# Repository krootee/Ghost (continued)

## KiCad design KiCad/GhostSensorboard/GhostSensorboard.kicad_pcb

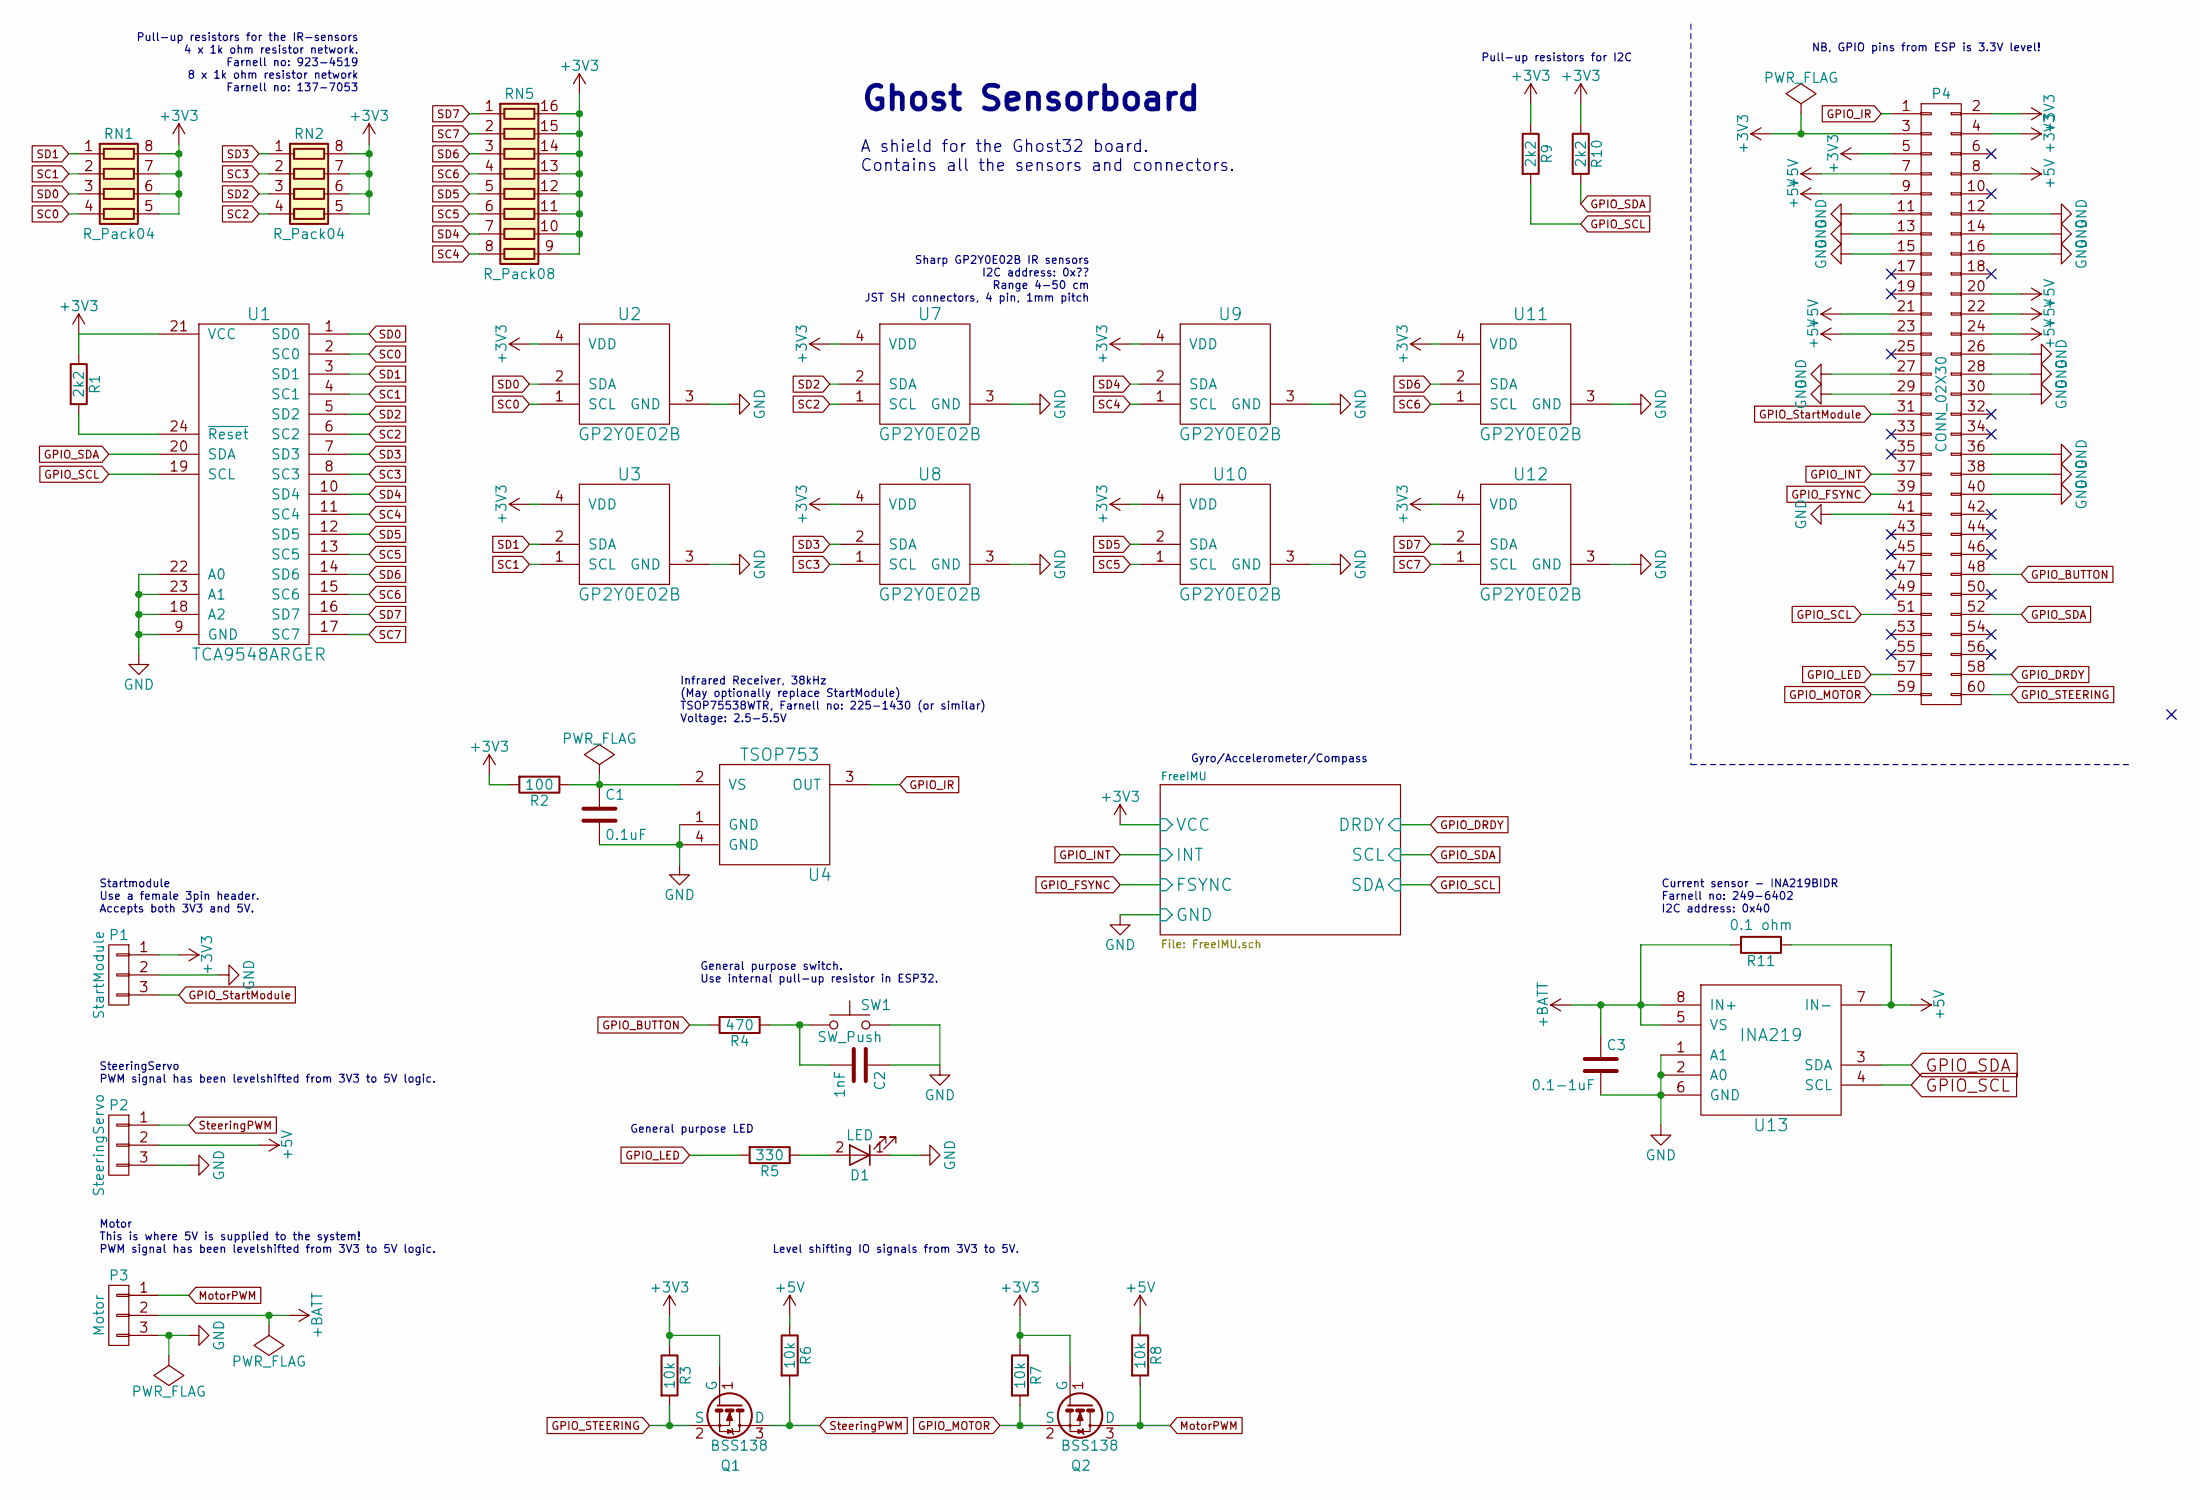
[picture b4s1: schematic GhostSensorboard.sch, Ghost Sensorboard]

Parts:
C1: 0.1uF; C_0603
C2: 1nF; C_0603
C3: 0.1-1uF; C_0603
D1: LED; LED_0805
P1: StartModule; Pin_Header_Straight_1x03_Pitch2.54mm
P2: SteeringServo; Pin_Header_Straight_1x03_Pitch2.54mm
P3: Motor; Pin_Header_Straight_1x03_Pitch2.54mm
P4: CONN_02X30; hrs-fx8c-60s-sv
Q1, Q2: BSS138; SOT-23
R1, R9, R10: 2k2; R_0603_HandSoldering
R2: 100; R_0603_HandSoldering
R3, R6, R7, R8: 10k; R_0603_HandSoldering
R4: 470; R_0603_HandSoldering
R5: 330; R_0603_HandSoldering
R11: 0.1 ohm; R_0603_HandSoldering
RN1, RN2: R_Pack04; R_Array_Convex_4x0603
RN5: R_Pack08; R_Array_Convex_8x0602
SW1: SW_Push; SW_SPST_EVQP2
U1: TCA9548ARGER; QFN-24_4x4mm_Pitch0.5mm
U2, U3, U7, U8, U9, U10, U11, U12: GP2Y0E02B; JST_SH_BM04B-SRSS-TB_04x1.00mm_Straight
U4: TSOP753; TSOP75x
U13: INA219; SOIC-8-N

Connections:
+3V3: P1.1, P4.2, P4.3, P4.4, P4.5, Q1.1 (G), Q2.1 (G), R1.1, R2.2, R3.1, R7.1, R9.1, R10.1, RN1.5 (R4.2), RN1.6 (R3.2), RN1.7 (R2.2), RN1.8 (R1.2), RN2.5 (R4.2), RN2.6 (R3.2), RN2.7 (R2.2), RN2.8 (R1.2), RN5.9 (R8.2), RN5.10 (R7.2), RN5.11 (R6.2), RN5.12 (R5.2), RN5.13 (R4.2), RN5.14 (R3.2), RN5.15 (R2.2), RN5.16 (R1.2), U1.21 (VCC), U2.4 (VDD), U3.4 (VDD), U7.4 (VDD), U8.4 (VDD), U9.4 (VDD), U10.4 (VDD), U11.4 (VDD), U12.4 (VDD); also elsewhere on the board
+5V: P2.2, P4.7, P4.8, P4.9, P4.20, P4.21, P4.22, P4.23, P4.24, R6.1, R8.1, R11.1, U13.7 (IN-)
+BATT: C3.1, P3.2, R11.2, U13.5 (VS), U13.8 (IN+)
GPIO_BUTTON: P4.48, R4.2
GPIO_DRDY: P4.58; also elsewhere on the board
GPIO_FSYNC: P4.39; also elsewhere on the board
GPIO_INT: P4.37; also elsewhere on the board
GPIO_IR: P4.1, U4.3 (OUT)
GPIO_LED: P4.57, R5.2
GPIO_MOTOR: P4.59, Q2.2 (S), R7.2
GPIO_SCL: P4.51, R9.2, U1.19 (SCL), U13.4 (SCL); also elsewhere on the board
GPIO_SDA: P4.52, R10.2, U1.20 (SDA), U13.3 (SDA); also elsewhere on the board
GPIO_STEERING: P4.60, Q1.2 (S), R3.2
GPIO_StartModule: P1.3, P4.31
MotorPWM: P3.1, Q2.3 (D), R8.2
unnamed: C1.1, R2.1, U4.2 (VS)
unnamed: C2.2, R4.1, SW1.1
unnamed: D1.2 (A), R5.1
unnamed: R1.2, U1.24 (~Reset)
SC0: RN1.4 (R4.1), U1.2 (SC0), U2.1 (SCL)
SC1: RN1.2 (R2.1), U1.4 (SC1), U3.1 (SCL)
SC2: RN2.4 (R4.1), U1.6 (SC2), U7.1 (SCL)
SC3: RN2.2 (R2.1), U1.8 (SC3), U8.1 (SCL)
SC4: RN5.8 (R8.1), U1.11 (SC4), U9.1 (SCL)
SC5: RN5.6 (R6.1), U1.13 (SC5), U10.1 (SCL)
SC6: RN5.4 (R4.1), U1.15 (SC6), U11.1 (SCL)
SC7: RN5.2 (R2.1), U1.17 (SC7), U12.1 (SCL)
SD0: RN1.3 (R3.1), U1.1 (SD0), U2.2 (SDA)
SD1: RN1.1 (R1.1), U1.3 (SD1), U3.2 (SDA)
SD2: RN2.3 (R3.1), U1.5 (SD2), U7.2 (SDA)
SD3: RN2.1 (R1.1), U1.7 (SD3), U8.2 (SDA)
SD4: RN5.7 (R7.1), U1.10 (SD4), U9.2 (SDA)
SD5: RN5.5 (R5.1), U1.12 (SD5), U10.2 (SDA)
SD6: RN5.3 (R3.1), U1.14 (SD6), U11.2 (SDA)
SD7: RN5.1 (R1.1), U1.16 (SD7), U12.2 (SDA)
SteeringPWM: P2.1, Q1.3 (D), R6.2

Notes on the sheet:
Ghost Sensorboard
A shield for the Ghost32 board. Contains all the sensors and connectors.
NB, GPIO pins from ESP is 3.3V level!
Startmodule Use a female 3pin header. Accepts both 3V3 and 5V.
Pull-up resistors for the IR-sensors 4 x 1k ohm resistor network. Farnell no: 923-4519 8 x 1k ohm resistor network Farnell no: 137-7053
Sharp GP2Y0E02B IR sensors I2C address: 0x?? Range 4-50 cm JST SH connectors, 4 pin, 1mm pitch
SteeringServo PWM signal has been levelshifted from 3V3 to 5V logic.
Motor This is where 5V is supplied to the system! PWM signal has been levelshifted from 3V3 to 5V logic.
Level shifting IO signals from 3V3 to 5V.
Current sensor - INA219BIDR Farnell no: 249-6402 I2C address: 0x40
General purpose switch. Use internal pull-up resistor in ESP32.
Infrared Receiver, 38kHz (May optionally replace StartModule) TSOP75538WTR, Farnell no: 225-1430 (or similar) Voltage: 2.5-5.5V
Pull-up resistors for I2C
General purpose LED
Gyro/Accelerometer/Compass

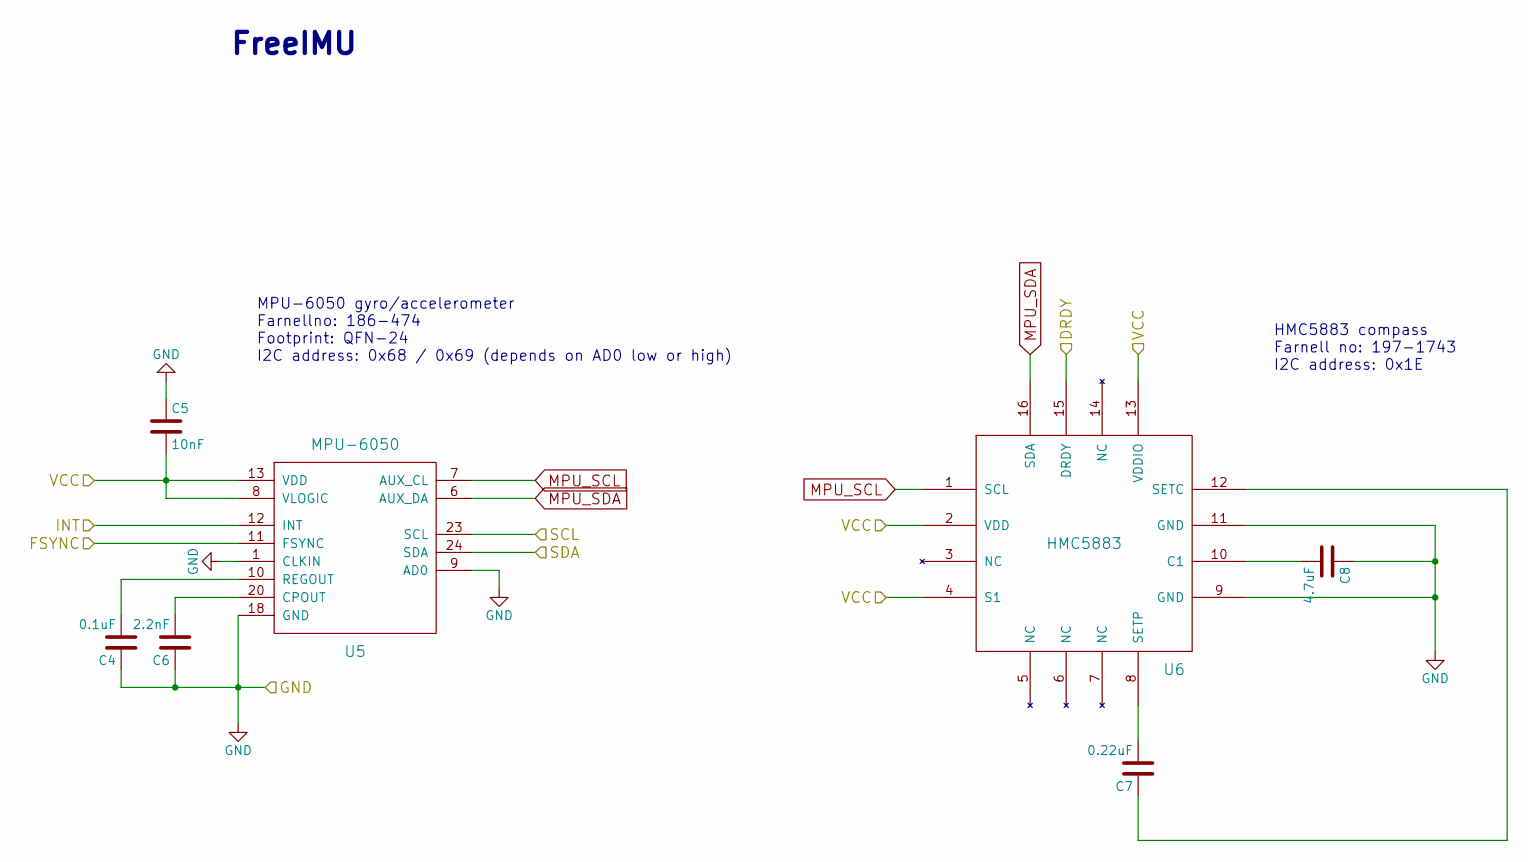
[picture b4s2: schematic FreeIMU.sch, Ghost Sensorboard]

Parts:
C4: 0.1uF; C_0603
C5: 10nF; C_0603
C6: 2.2nF; C_0603
C7: 0.22uF; C_0603
C8: 4.7uF; C_0603
U5: MPU-6050; QFN-24-1EP_4x4mm_Pitch0.5mm
U6: HMC5883

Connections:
+3V3: C5.2, U5.8 (VLOGIC), U5.13 (VDD), U6.2 (VDD), U6.4 (S1), U6.13 (VDDIO); also elsewhere on the board
GPIO_DRDY: U6.15 (DRDY); also elsewhere on the board
GPIO_FSYNC: U5.11 (FSYNC); also elsewhere on the board
GPIO_INT: U5.12 (INT); also elsewhere on the board
GPIO_SCL: U5.24 (SDA); also elsewhere on the board
GPIO_SDA: U5.23 (SCL); also elsewhere on the board
MPU_SCL: U5.7 (AUX_CL), U6.1 (SCL)
MPU_SDA: U5.6 (AUX_DA), U6.16 (SDA)
unnamed: C4.2, U5.10 (REGOUT)
unnamed: C6.2, U5.20 (CPOUT)
unnamed: C7.1, U6.12 (SETC)
unnamed: C7.2, U6.8 (SETP)
unnamed: C8.2, U6.10 (C1)

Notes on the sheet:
MPU-6050 gyro/accelerometer Farnellno: 186-474 Footprint: QFN-24 I2C address: 0x68 / 0x69 (depends on AD0 low or high)
FreeIMU
HMC5883 compass Farnell no: 197-1743 I2C address: 0x1E

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
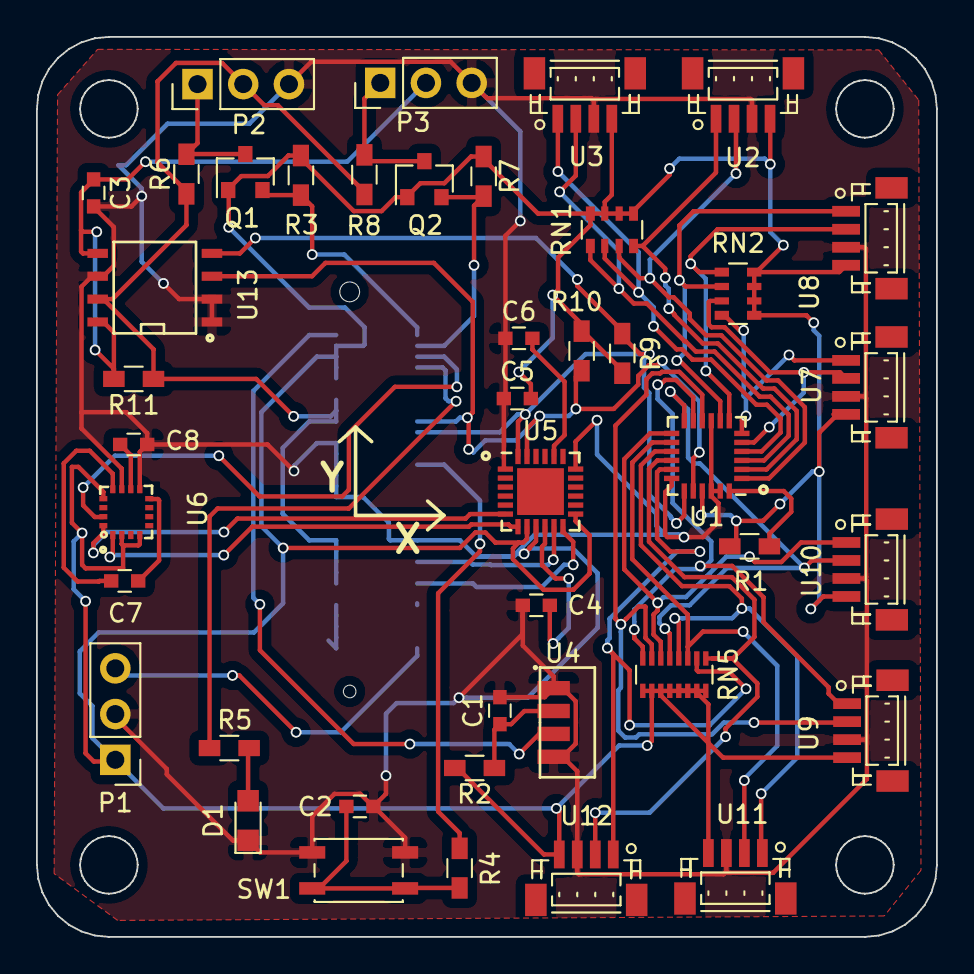
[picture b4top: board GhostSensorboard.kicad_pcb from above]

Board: 2 copper layers, 50.0 x 50.0 mm, 43 parts (1 on the bottom side), 44 nets.

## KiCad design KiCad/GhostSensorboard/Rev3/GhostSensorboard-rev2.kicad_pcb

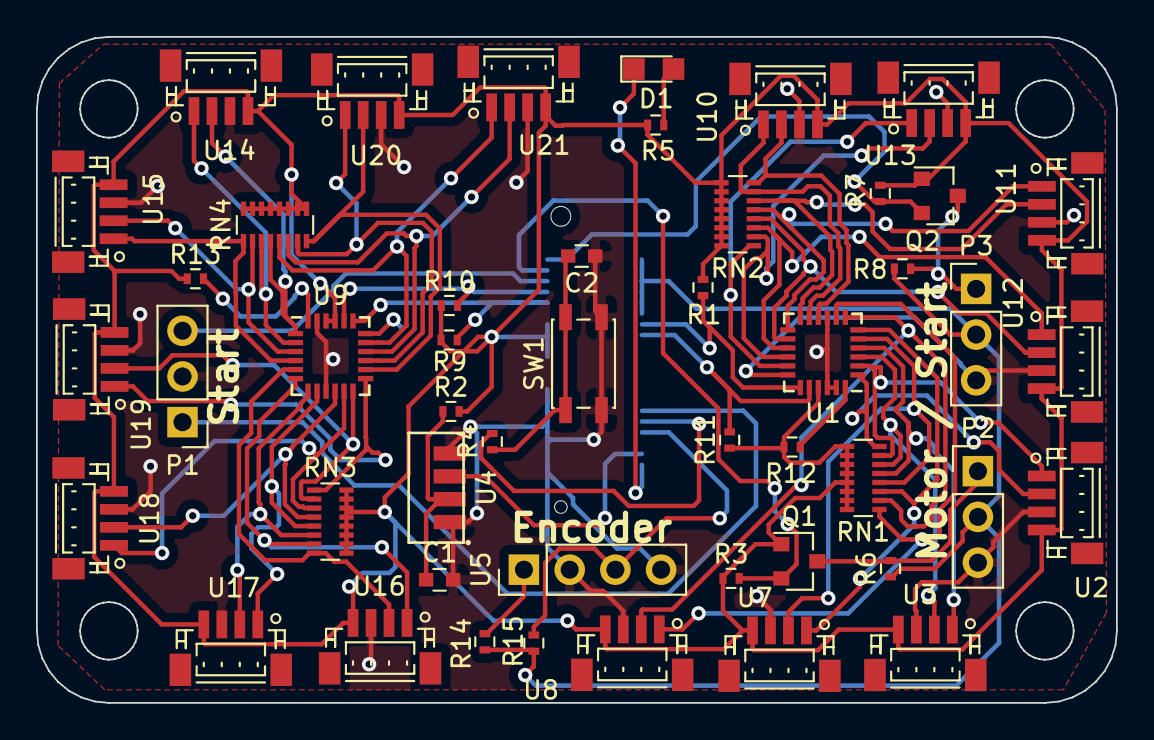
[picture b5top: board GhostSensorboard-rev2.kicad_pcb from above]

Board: 2 copper layers, 60.0 x 37.0 mm, 49 parts (1 on the bottom side), 55 nets.

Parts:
C1: 0.1uF; C_0603
C2: 1nF; C_0603
D1: LED; LED_0805
J2: CONN_02X20; hrs-fx8c-40s-sv5
P1: StartModule; Pin_Header_Straight_1x03_Pitch2.54mm
P2: SteeringServo; Pin_Header_Straight_1x03_Pitch2.54mm
P3: Motor; Pin_Header_Straight_1x03_Pitch2.54mm
Q1, Q2: BSS138; SOT-23
R1, R9, R10, R11, R12, R13: 2k2; R_0402
R2: 100; R_0402
R3, R6, R7, R8, R15: 10k; R_0402
R4: 470; R_0402
R5: 330; R_0402
R14: 270; R_0402
RN1, RN2, RN3, RN4: R_Pack08; R_Array_Convex_8x0602
SW1: SW_Push; SW_SPST_EVQP2
U1, U9: TCA9548ARGER; QFN-24_4x4mm_Pitch0.5mm
U2, U3, U7, U8, U10, U11, U12, U13, U14, U15, U16, U17, U18, U19, U20, U21: GP2Y0E02B; JST_SH_BM04B-SRSS-TB_04x1.00mm_Straight
U4: TSOP753; TSOP75x
U5: Transmissive_Photo_Interrupter; Pin_Header_Straight_1x04_Pitch2.54mm

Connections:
+3V3: J2.7, J2.8, J2.9, J2.10, Q1.1, Q2.1, R1.1, R2.2, R3.1, R5.2, R7.1, R9.1, R10.1, R11.1, R12.1, R13.1, RN1.9, RN1.10, RN1.11, RN1.12, RN1.13, RN1.14, RN1.15, RN1.16, RN2.9, RN2.10, RN2.11, RN2.12, RN2.13, RN2.14, RN2.15, RN2.16, RN3.9, RN3.10, RN3.11, RN3.12, RN3.13, RN3.14, RN3.15, RN3.16, RN4.9, RN4.10, RN4.11, RN4.12, RN4.13, RN4.14, RN4.15, RN4.16, U1.21, U2.4, U3.4, U7.4, U8.4, U9.21, U9.22, U10.4, U11.4, U12.4, U13.4, U14.4, U15.4, U16.4, U17.4, U18.4, U19.4, U20.4, U21.4
+5V: J2.35, J2.36, J2.37, J2.38, J2.39, J2.40, P2.2, P3.2, R6.1, R8.1, R14.2, R15.1
BUTTON: J2.25, R4.2
ENCODER: J2.24, R15.2, U5.3
GND: C1.2, C2.1, J2.13, J2.14, J2.15, J2.16, J2.17, J2.18, J2.19, J2.20, P1.2, P2.3, P3.3, SW1.2, U1.9, U1.18, U1.22, U1.23, U2.3, U3.3, U4.1, U4.4, U5.2, U5.4, U7.3, U8.3, U9.9, U9.18, U9.23, U10.3, U11.3, U12.3, U13.3, U14.3, U15.3, U16.3, U17.3, U18.3, U19.3, U20.3, U21.3
IO13: J2.33, R11.2, U1.20
IO14: J2.34, R1.2, U1.19
IO17: J2.26, P1.1
IO22: J2.22, U4.3
IO25: J2.3, P1.3
IO26: J2.2, Q1.2, R3.2
IO27: J2.1, Q2.2, R7.2
IO32: J2.5, R9.2, U9.19
IO33: J2.4, R10.2, U9.20
LED: D1.1, J2.21
MOTOR_5V_PWM: P3.1, Q2.3, R8.2
unnamed: C1.1, R2.1, U4.2
unnamed: C2.2, R4.1, SW1.1
unnamed: D1.2, R5.1
unnamed: R12.2, U1.24
unnamed: R13.2, U9.24
unnamed: R14.1, U5.1
SC0: RN1.7, U1.2, U2.1
SC1: RN1.5, U1.4, U3.1
SC2: RN1.3, U1.6, U7.1
SC3: RN1.1, U1.8, U8.1
SC4: RN2.7, U1.11, U10.1
SC5: RN2.5, U1.13, U11.1
SC6: RN2.3, U1.15, U12.1
SC7: RN2.1, U1.17, U13.1
SC8: RN4.3, U9.2, U14.1
SC9: RN4.1, U9.4, U15.1
SC10: RN3.7, U9.6, U16.1
SC11: RN3.5, U9.8, U17.1
SC12: RN3.3, U9.11, U18.1
SC13: RN3.1, U9.13, U19.1
SC14: RN4.7, U9.15, U20.1
SC15: RN4.5, U9.17, U21.1
SD0: RN1.8, U1.1, U2.2
SD1: RN1.6, U1.3, U3.2
SD2: RN1.4, U1.5, U7.2
SD3: RN1.2, U1.7, U8.2
SD4: RN2.8, U1.10, U10.2
SD5: RN2.6, U1.12, U11.2
SD6: RN2.4, U1.14, U12.2
SD7: RN2.2, U1.16, U13.2
SD8: RN4.4, U9.1, U14.2
SD9: RN4.2, U9.3, U15.2
SD10: RN3.8, U9.5, U16.2
SD11: RN3.6, U9.7, U17.2
SD12: RN3.4, U9.10, U18.2
SD13: RN3.2, U9.12, U19.2
SD14: RN4.8, U9.14, U20.2
SD15: RN4.6, U9.16, U21.2
STEERING_5V_PWM: P2.1, Q1.3, R6.2
